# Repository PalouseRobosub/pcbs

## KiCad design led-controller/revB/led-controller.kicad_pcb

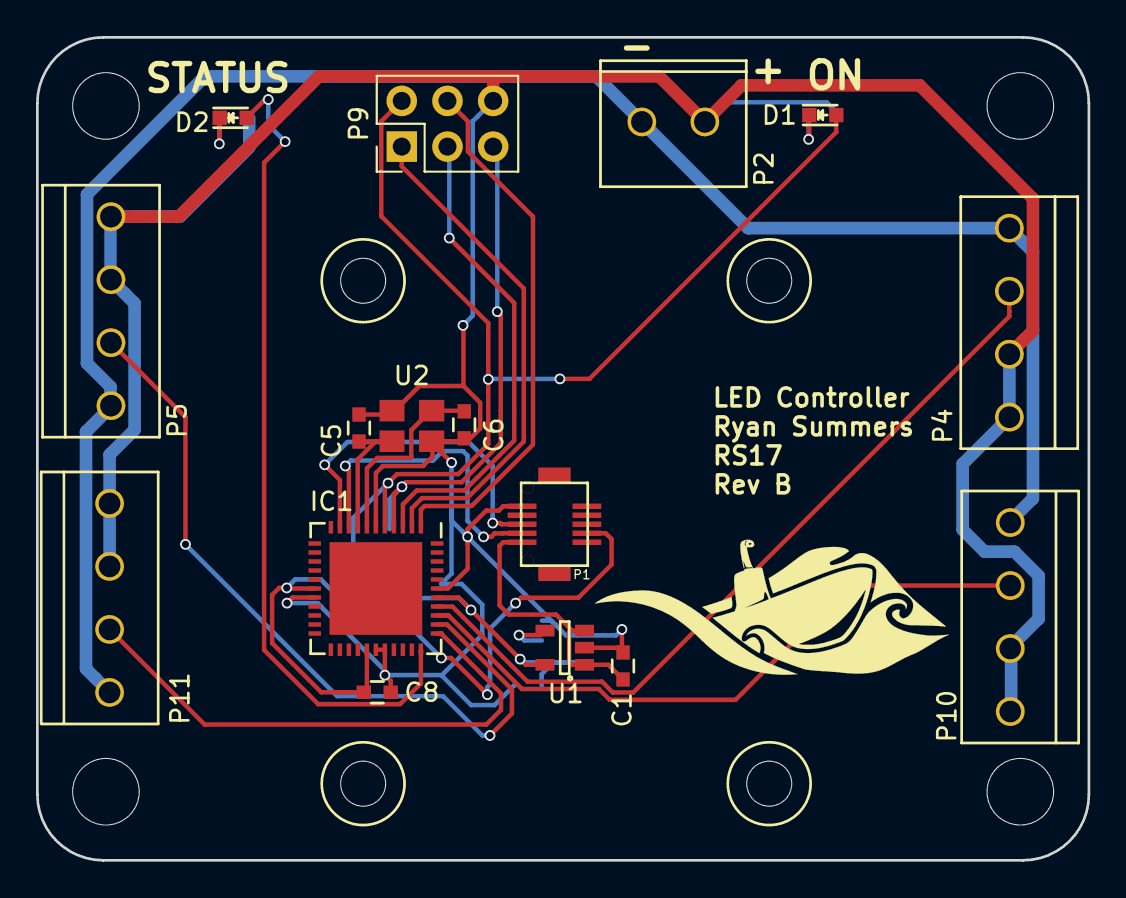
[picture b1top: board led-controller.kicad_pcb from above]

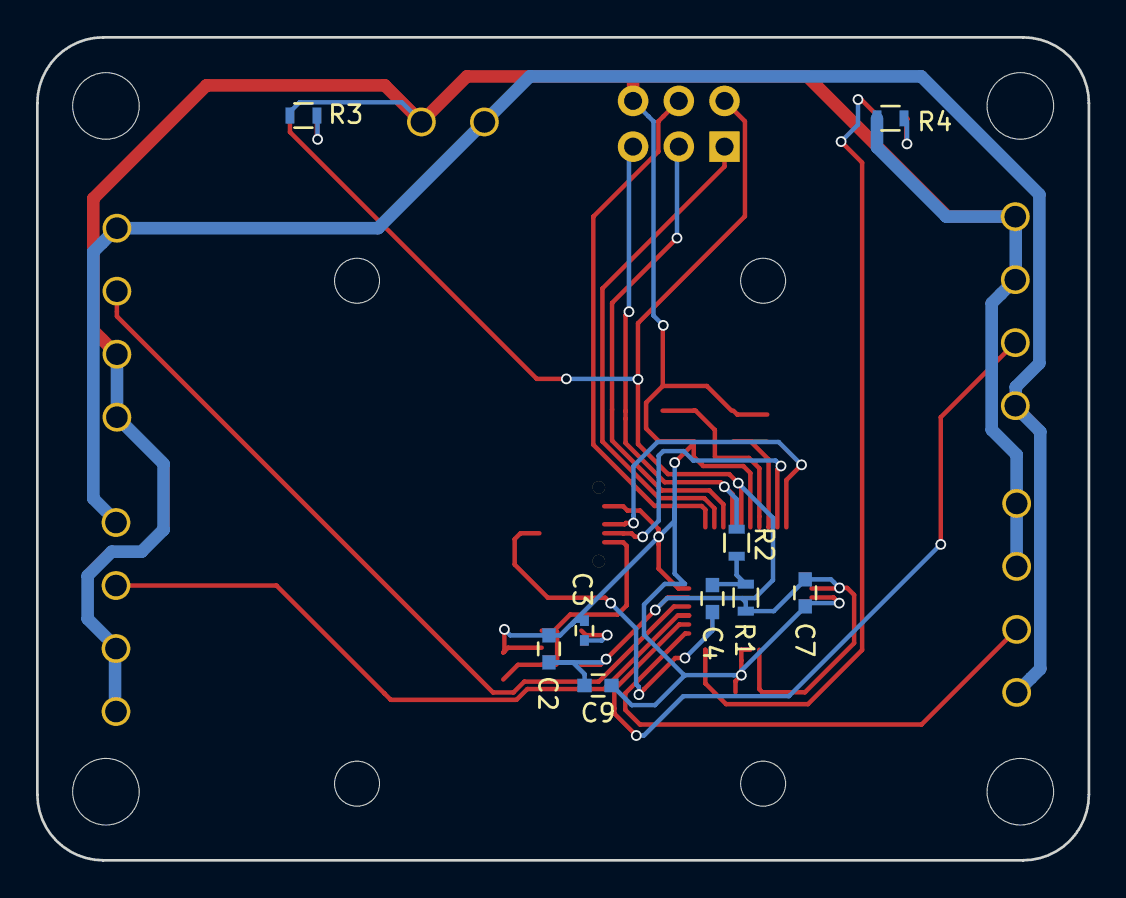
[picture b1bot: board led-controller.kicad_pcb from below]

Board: 2 copper layers, 58.4 x 45.7 mm, 29 parts (9 on the bottom side), 22 nets.

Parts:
C1: 1uF; C_0603
C2: 2.2uF; C_0603
C3: 100p; C_0402
C4: 100nF; C_0603
C5, C6: 18p; C_0603
C7, C8: 100n; C_0603
C9: 4.7u; C_0603
D1, D2: LED; LED_0603
IC1: ATMEGA1284P-M; QFN-44-1EP_7x7mm_Pitch0.5mm
P1: Mezzanine-Header; 3mm-10pos-receptacle
P2: Conn; Screw-Terminal-2-3.5mm
P3, P6, P7, P8: Spacer; 3mm-support
P4, P5, P10, P11: CONN_01X04; Screw-Terminal-4-3.5mm
P9: CONN_02X03; Pin_Header_Straight_2x03_Pitch2.54mm
R1: 10k; R_0603
R2: 1k; R_0603
R3, R4: 65; R_0603
U1: AP2210; SOT-23-5
U2: TSX-3225; DFN-4

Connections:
+3V3: C2.1, C7.1, C8.1, C9.1, D1.2, IC1.5, IC1.17, IC1.27, IC1.38, P9.2, R1.1, U1.5
+5V: C1.1, P1.1, U1.1, U1.3
/DTR: C4.2, P1.4
/RX_CPU: IC1.10, P1.5
/TX_CPU: IC1.9, P1.3
/led_pwr: P2.1, P4.1, P5.1, P10.1, P11.1
/microcontroller/DBG_LED: D2.2, IC1.33
/microcontroller/MISO: IC1.2, P9.1
/microcontroller/MOSI: IC1.1, P9.4
/microcontroller/SCK: IC1.3, P9.3
/microcontroller/~RST: IC1.4, P9.5, R2.1
/signal1: IC1.37, P4.2
/signal2: IC1.36, P10.2
/signal3: IC1.35, P5.2
/signal4: IC1.34, P11.2
GND: C1.2, C2.2, C3.2, C5.2, C6.2, C7.2, C8.2, C9.2, IC1.6, IC1.18, IC1.28, IC1.29, IC1.39, P1.9, P2.2, P4.3, P4.4, P5.3, P5.4, P9.6, P10.3, P10.4, P11.3, P11.4, R3.2, R4.2, U1.2, U2.2, U2.4
unnamed: C3.1, U1.4
unnamed: C4.1, R1.2, R2.2
unnamed: C5.1, IC1.8, U2.3
unnamed: C6.1, IC1.7, U2.1
unnamed: D1.1, R3.1
unnamed: D2.1, R4.1

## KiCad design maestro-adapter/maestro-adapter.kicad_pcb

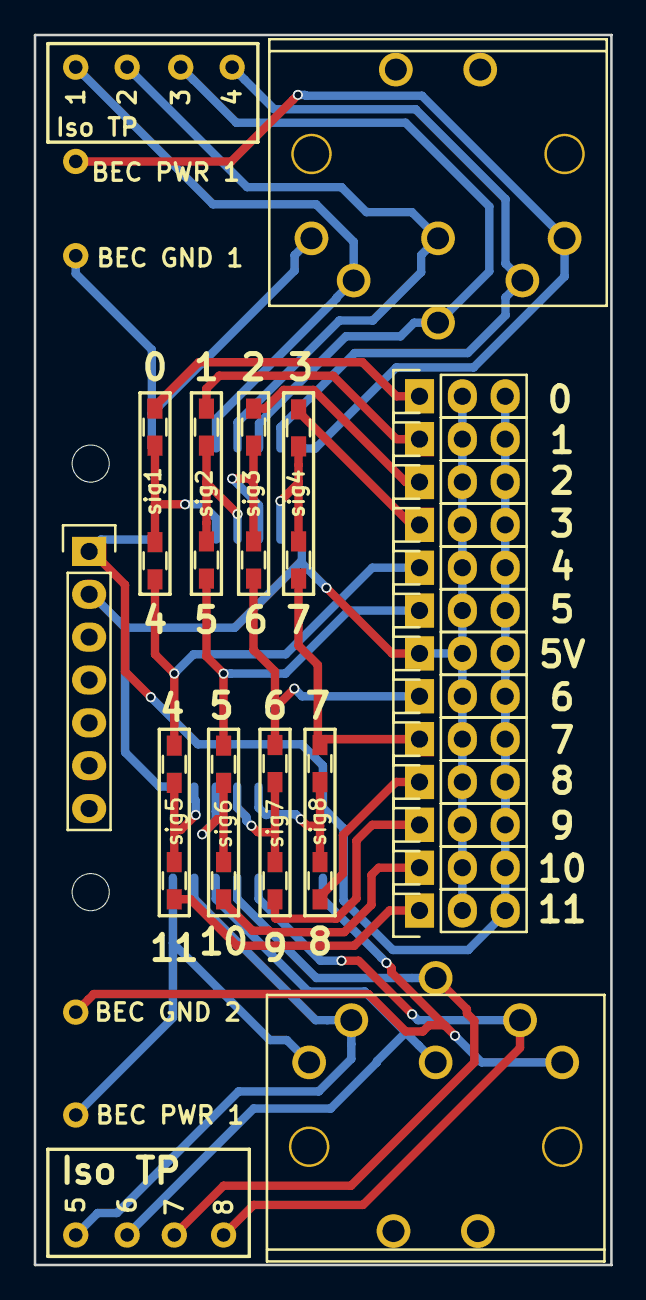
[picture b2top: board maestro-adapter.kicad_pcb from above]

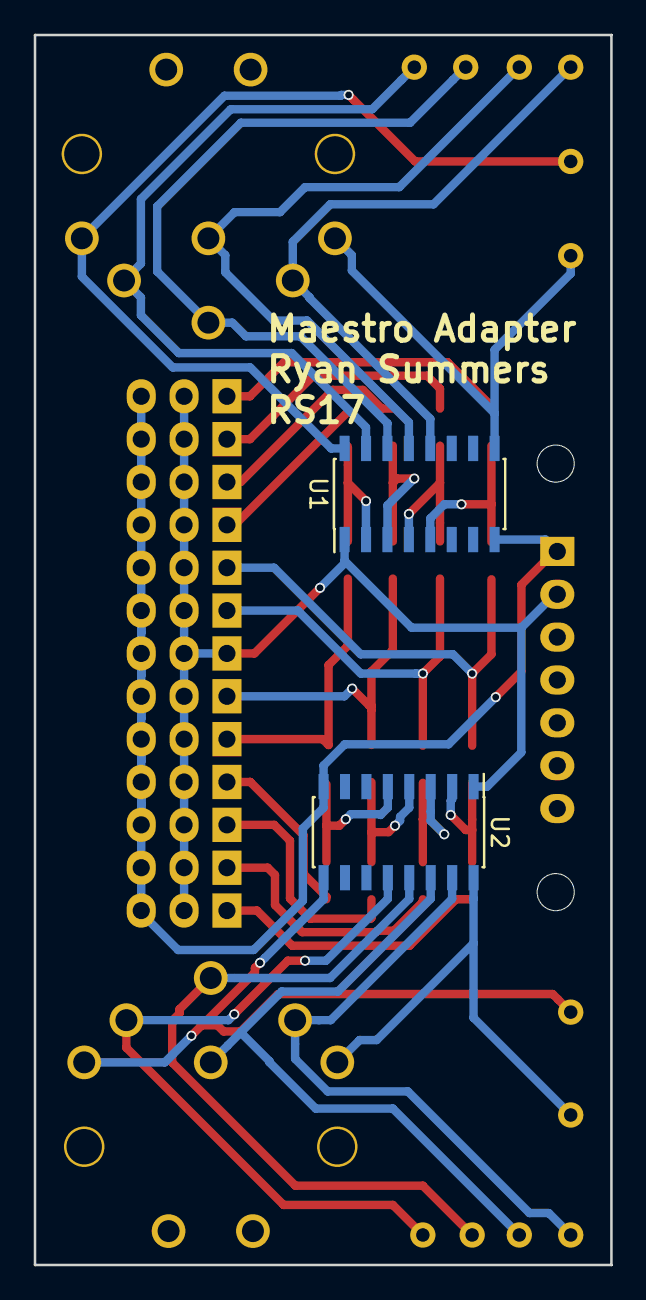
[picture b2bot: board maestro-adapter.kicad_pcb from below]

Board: 2 copper layers, 34.2 x 72.9 mm, 46 parts (2 on the bottom side), 34 nets.

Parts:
P1: CONN_01X07; Pin_Header_Straight_1x07
P2, P3, P4, P5, P6, P7, P8, P9, P10, P11, P12, P13, P16: CONN_01X03; Pin_Header_Straight_1x03
P14, P15: CONN_01X06; cui-6-board-f
R1, R2, R3, R4, R5, R6, R7, R8, R9, R10, R11, R12, R13, R14, R15, R16: 0; R_0603_HandSoldering
U1, U2: Si866x; SOIC-16_3.9x9.9mm_Pitch1.27mm
W1, W2, W3, W4, W5, W6, W7, W8, W9, W10, W11, W12: TEST_1P; Measurement_Point_Round-TH_Small

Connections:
+5V: P1.2, P2.2, P3.2, P4.2, P5.2, P6.2, P7.2, P8.2, P9.2, P10.2, P11.2, P12.2, P13.2, P16.1, P16.2, U1.1, U2.1
/bec_esc_1: P14.3, U1.16, W9.1
/bec_esc_2: P15.3, U2.16, W10.1
/bec_gnd_1: P14.1, U1.9, W11.1
/bec_gnd_2: P15.1, U2.9, W12.1
/sig1: P8.1, R1.2
/sig1_in: R1.1, R9.2, U1.5
/sig1_isolated: P14.4, U1.12, W1.1
/sig2: P7.1, R2.2
/sig2_in: R2.1, R10.2, U1.4
/sig2_isolated: P14.2, U1.13, W2.1
/sig3: P10.1, R3.2
/sig3_in: R3.1, R11.2, U1.3
/sig3_isolated: P14.6, U1.14, W3.1
/sig4: P11.1, R4.2
/sig4_in: R4.1, R12.2, U1.2
/sig4_isolated: P14.5, U1.15, W4.1
/sig5: P12.1, R5.2
/sig5_in: R5.1, R13.1, U2.2
/sig5_isolated: P15.5, U2.15, W5.1
/sig6: P13.1, R6.2
/sig6_in: R6.1, R14.1, U2.3
/sig6_isolated: P15.2, U2.14, W6.1
/sig7: P5.1, R7.2
/sig7_in: R7.1, R15.1, U2.4
/sig7_isolated: P15.6, U2.13, W7.1
/sig8: P6.1, R8.2
/sig8_in: R8.1, R16.1, U2.5
/sig8_isolated: P15.4, U2.12, W8.1
/t1: P2.1, R9.1, R13.2
/t2: P3.1, R10.1, R14.2
/t3: P4.1, R11.1, R15.2
/t4: P9.1, R12.1, R16.2
GND: P1.1, P2.3, P3.3, P4.3, P5.3, P6.3, P7.3, P8.3, P9.3, P10.3, P11.3, P12.3, P13.3, P16.3, U1.8, U2.8

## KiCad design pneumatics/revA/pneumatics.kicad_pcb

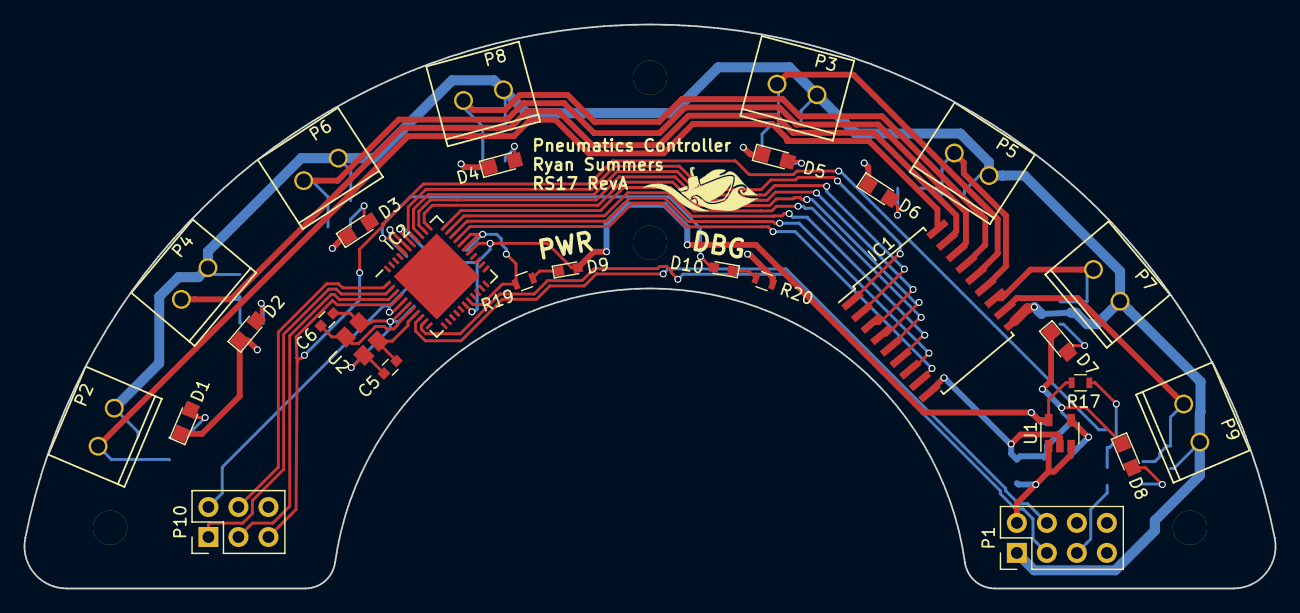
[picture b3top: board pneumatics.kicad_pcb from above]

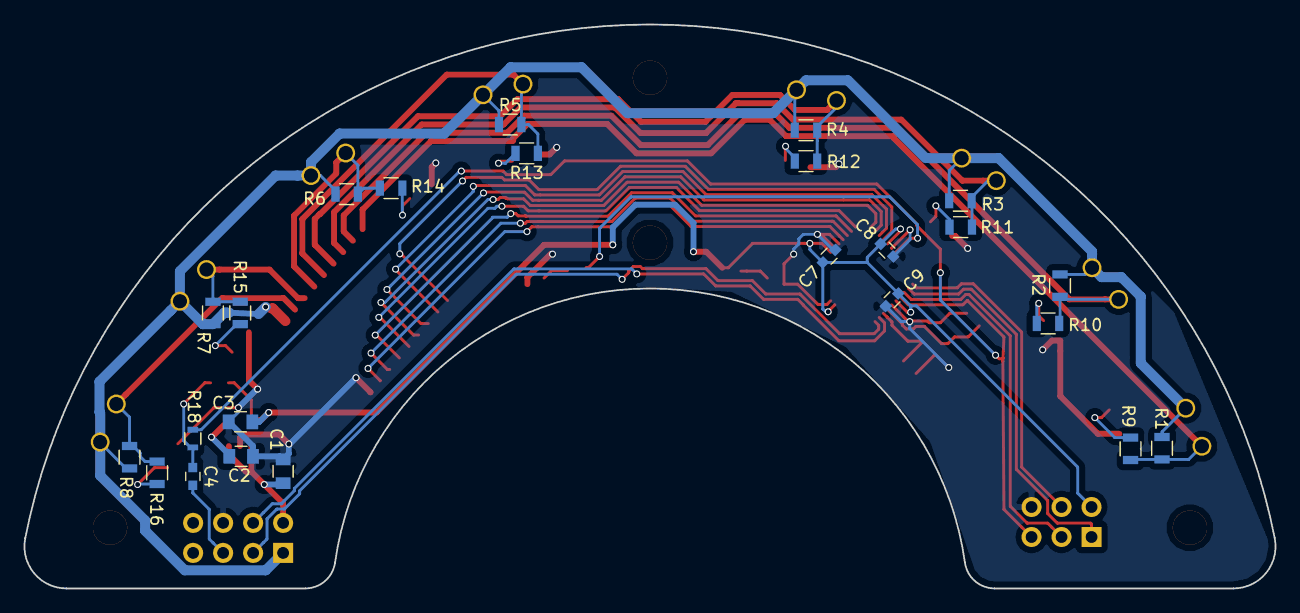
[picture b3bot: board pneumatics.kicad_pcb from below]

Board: 2 copper layers, 105.9 x 47.8 mm, 53 parts (24 on the bottom side), 42 nets.

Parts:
C1: 1u; C_0805
C2: 100p; C_0805
C3: 2.2u; C_0805
C4: 100nF; C_0603
C5, C6: 18p; C_0603
C7, C8: 100n; C_0603
C9: 4.7u; C_0603
D1, D2, D3, D4, D5, D6, D7, D8: YLW; LED_0805
D9, D10: LED; LED_0603
IC1: ULN2803A; SOIC-18W_7.5x11.6mm_Pitch1.27mm
IC2: ATMEGA1284P-M; QFN-44-1EP_7x7mm_Pitch0.5mm
P1: CONN_01X06; Pin_Header_Straight_2x04_Pitch2.54mm
P2, P3, P4, P5, P6, P7, P8, P9: CONN_01X02; Screw-Terminal-2-3.5mm
P10: CONN_02X03; Pin_Header_Straight_2x03_Pitch2.54mm
R1, R2, R3, R4, R5, R6, R7, R8, R9, R10, R11, R12, R13, R14, R15, R16: R; R_0805
R17: 10k; R_0603
R18: 1k; R_0603
R19, R20: 65; R_0603
U1: AP2210; SOT-23-5
U2: TSX-3225; DFN-4

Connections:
+3V3: C3.1, C7.1, C8.1, C9.1, D9.2, IC2.5, IC2.17, IC2.27, IC2.38, P10.2, R17.1, U1.5
+5V: C1.1, P1.2, U1.1, U1.3
+12V: IC1.10, P1.1, P2.1, P3.1, P4.1, P5.1, P6.1, P7.1, P8.1, P9.1, R1.1, R2.1, R3.1, R4.1, R5.1, R6.1, R7.1, R8.1
/Microcontroller/DBG_LED: D10.2, IC2.40
/Microcontroller/MISO: IC2.2, P10.1
/Microcontroller/MOSI: IC2.1, P10.4
/Microcontroller/SCK: IC2.3, P10.3
/Microcontroller/~RST: IC2.4, P10.5, R18.1
/PC1: IC1.1, IC2.37
/PC2: IC1.2, IC2.36
/PC3: IC1.3, IC2.35
/PC4: IC1.4, IC2.34
/PC5: IC1.5, IC2.33
/PC6: IC1.6, IC2.32
/PC7: IC1.7, IC2.31
/PC8: IC1.8, IC2.30
/PN1: IC1.18, P2.2, R1.2, R9.1
/PN2: IC1.17, P4.2, R2.2, R10.1
/PN3: IC1.16, P6.2, R3.2, R11.1
/PN4: IC1.15, P8.2, R4.2, R12.1
/PN5: IC1.14, P3.2, R5.2, R13.1
/PN6: IC1.13, P5.2, R6.2, R14.1
/PN7: IC1.12, P7.2, R7.2, R15.1
/PN8: IC1.11, P9.2, R8.2, R16.1
/dtr: C4.2, P1.5
/rx_cpu: IC2.10, P1.3
/tx_cpu: IC2.9, P1.4
GND: C1.2, C2.2, C3.2, C5.2, C6.2, C7.2, C8.2, C9.2, D1.1, D2.1, D3.1, D4.1, D5.1, D6.1, D7.1, D8.1, IC1.9, IC2.6, IC2.18, IC2.28, IC2.29, IC2.39, P1.6, P10.6, R19.2, R20.2, U1.2, U2.2, U2.4
unnamed: C2.1, U1.4
unnamed: C4.1, R17.2, R18.2
unnamed: C5.1, IC2.8, U2.3
unnamed: C6.1, IC2.7, U2.1
unnamed: D1.2, R9.2
unnamed: D2.2, R10.2
unnamed: D3.2, R11.2
unnamed: D4.2, R12.2
unnamed: D5.2, R13.2
unnamed: D6.2, R14.2
unnamed: D7.2, R15.2
unnamed: D8.2, R16.2
unnamed: D9.1, R19.1
unnamed: D10.1, R20.1

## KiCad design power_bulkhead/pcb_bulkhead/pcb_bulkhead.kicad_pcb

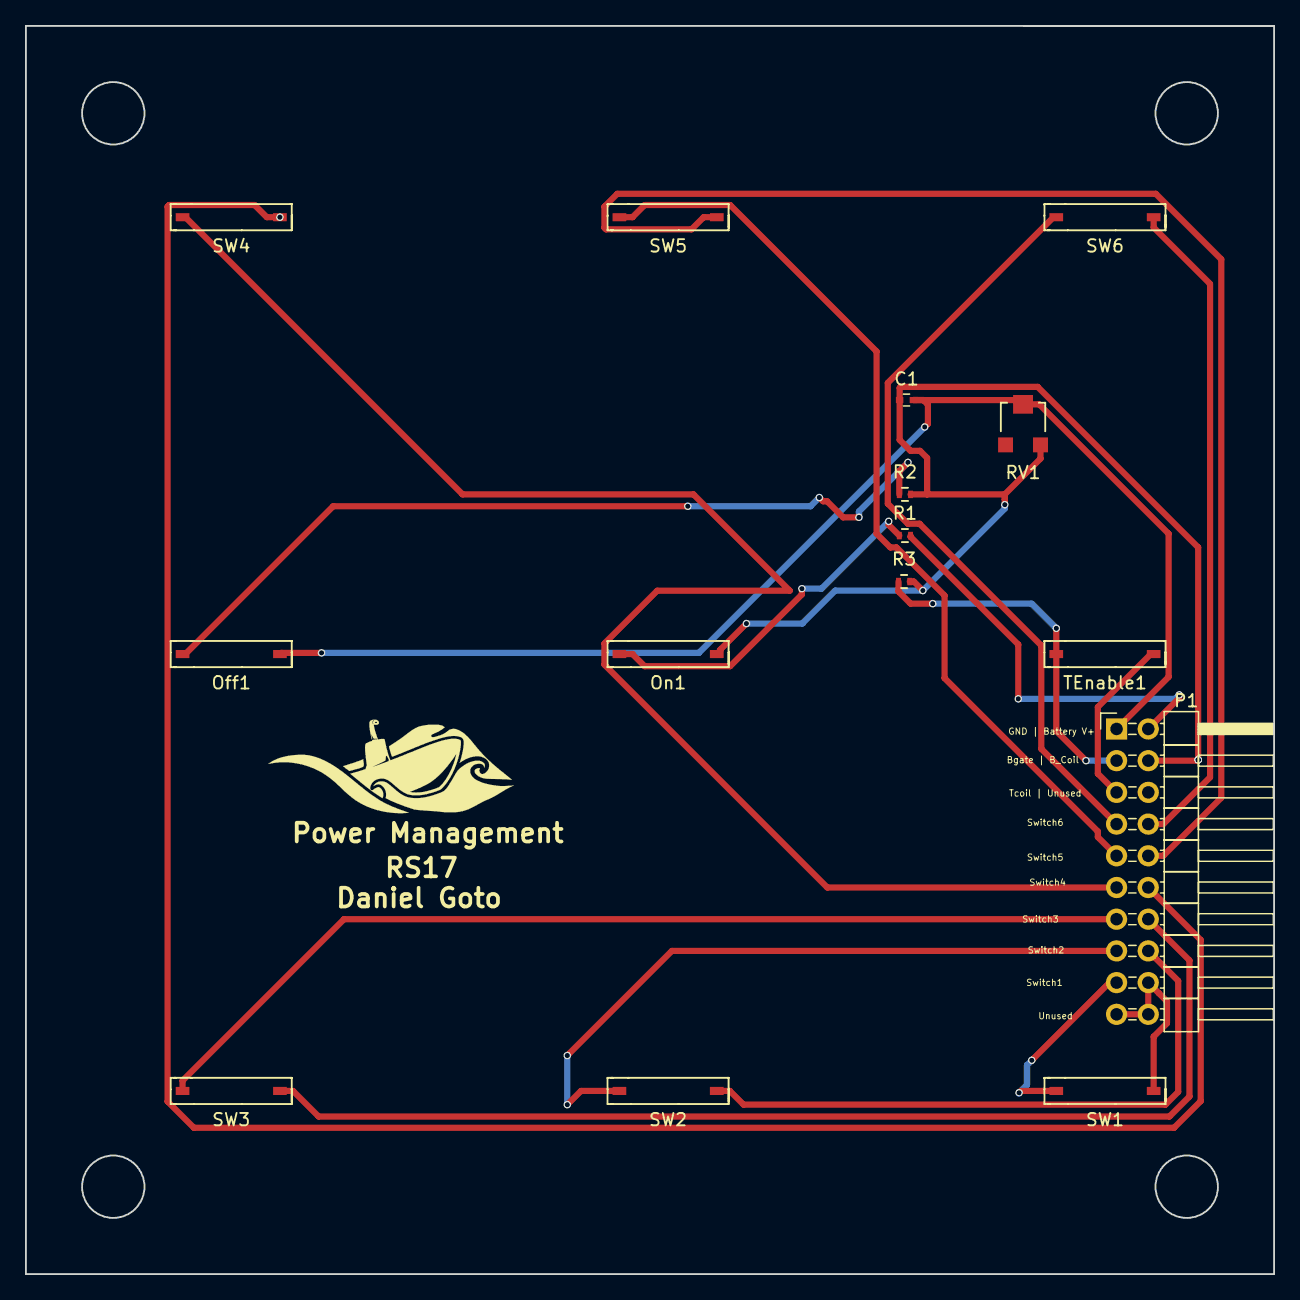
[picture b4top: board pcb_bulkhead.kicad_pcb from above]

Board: 2 copper layers, 100.0 x 100.0 mm, 15 parts (0 on the bottom side), 19 nets.

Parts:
C1: 10u; C_0402
Off1: SW_PUSH; MK17-reed-switch
On1: SW_PUSH; MK17-reed-switch
P1: CONN_01X17; Pin_Header_Angled_2x10_Pitch2.54mm
R1: 20k; R_0402
R2: 1k; R_0402
R3: 15k; R_0402
RV1: POT; Potentiometer_Trimmer-EVM3E
SW1, SW2, SW3, SW4, SW5, SW6: SW_PUSH; MK17-reed-switch
TEnable1: SW_PUSH; MK17-reed-switch

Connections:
Battery+: P1.2, R1.2
Bulkhead+: P1.3, R3.1, TEnable1.1
BulkheadCoil: C1.1, On1.2, P1.4, R2.2, R3.2, RV1.3
GND: C1.2, Off1.2, P1.1, RV1.2
unnamed: Off1.1, R2.1
unnamed: On1.1, R1.1
unnamed: P1.6, SW6.2
unnamed: P1.7, SW6.1
unnamed: P1.8, SW5.2
unnamed: P1.9, SW5.1
unnamed: P1.10, SW4.2
unnamed: P1.11, SW4.1
unnamed: P1.12, SW3.2
unnamed: P1.13, SW3.1
unnamed: P1.14, SW2.2
unnamed: P1.15, SW2.1
unnamed: P1.16, SW1.2
unnamed: P1.17, SW1.1
ThrusterCoil: P1.5, TEnable1.2

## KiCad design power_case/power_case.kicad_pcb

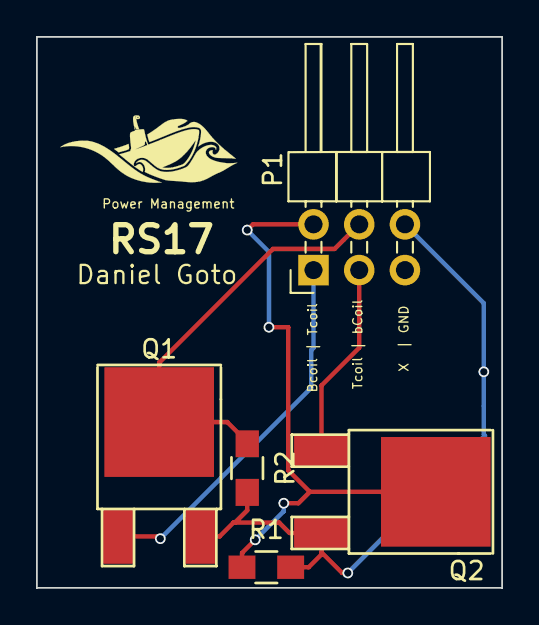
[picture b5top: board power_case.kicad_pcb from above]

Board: 2 copper layers, 25.8 x 30.6 mm, 5 parts (0 on the bottom side), 5 nets.

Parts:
P1: CONN_02X03; Pin_Header_Angled_2x03_Pitch2.54mm_new
Q1, Q2: Q_NJFET_DGS; TO-252-2Lead
R1, R2: 5k; R_0805_HandSoldering

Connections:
GND: P1.6, Q1.3, Q2.3, R1.2, R2.2
unnamed: P1.2, Q2.2, R1.1
unnamed: P1.4, Q1.2, R2.1
Tcoil: P1.3, Q2.1
bCoil: P1.1, Q1.1

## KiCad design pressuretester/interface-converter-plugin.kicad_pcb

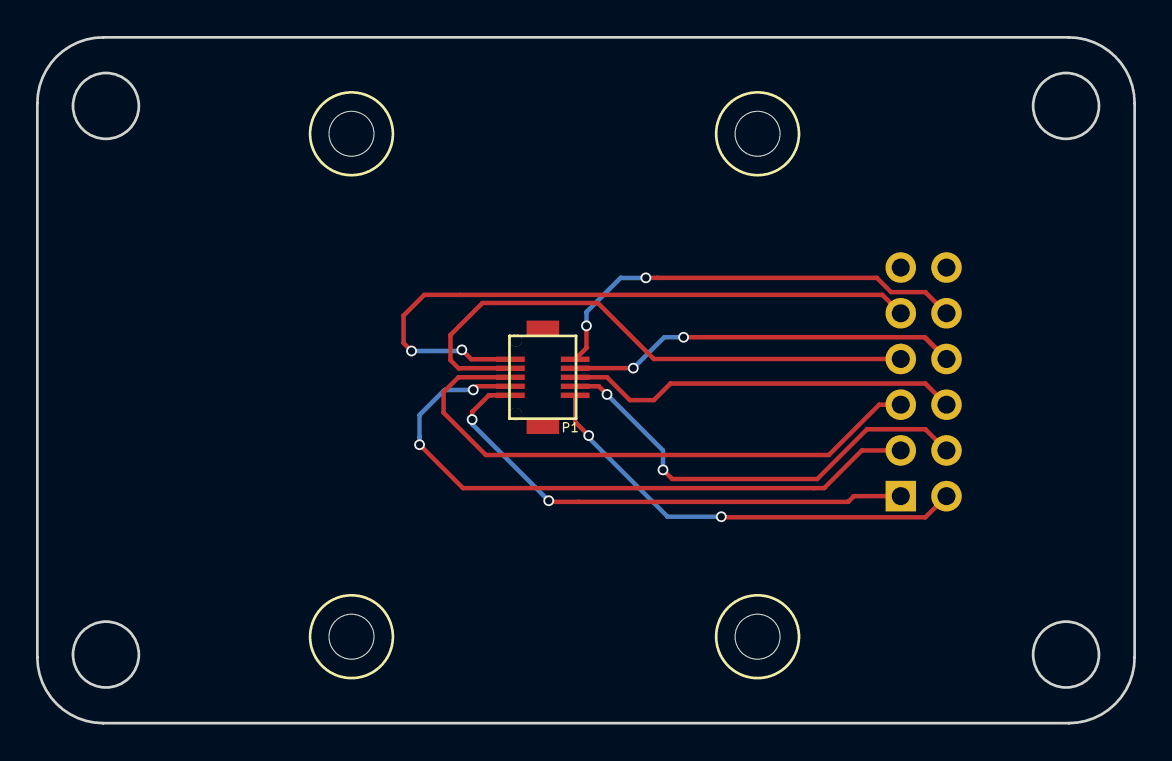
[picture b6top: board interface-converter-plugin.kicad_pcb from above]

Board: 2 copper layers, 61.0 x 38.1 mm, 6 parts (1 on the bottom side), 10 nets.

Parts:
P1: Mezzanine-Header; 3mm-10pos-receptacle
P2: CONN_02X06; Pin_Header_Angled_2x06_Pitch2.54mm
U1, U2, U3, U4: 3mm-support

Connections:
/AC3: P1.6, P2.6
/AC4: P1.8, P2.8
/AC5: P1.10, P2.10
/CS: P1.2, P2.2
/DTR: P1.4, P2.4
/GND: P1.9, P2.9
/RX/SDO: P1.5, P2.5
/SDI: P1.7, P2.7
/TX/SCK: P1.3, P2.3
/Vbus: P1.1, P2.1
